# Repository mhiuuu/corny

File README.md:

# Corny Split Keyboard

My first custom split keyboard that takes inspiration from the [Corne keyboard](https://www.boardsource.xyz/products/Corne).

---

## Motivation

I’m pretty much a geek who always finds ways to create things tailored specifically for myself. I've been using Arch Linux (BTW), Hyprland (BTW), and Neovim (BTW) for over a year now, and most of my workflow depends heavily on the keyboard.

Over time, I’ve tried 60%, 75%, and 100% mechanical keyboards. They’re all nice, but I struggled to find space on my desk for schoolwork, and placing the keyboard on my laptop caused the battery to heat up. Then one day, I stumbled upon [this video](https://youtu.be/7UXsD7nSfDY?si=9aiY0pJiT80jEVwv), which sparked the idea—and here it is: my first-ever custom-built split keyboard. All the design work was done in less than 5 days.

---

## Build

This keyboard was created using [Ergogen](https://github.com/ergogen/ergogen), with extra helpful guidance from the [Flatfootfox tutorial](https://flatfootfox.com) and HunterCook—a genius and my friend on Discord.

The design is entirely customized for my hand movements and habits. It may not suit your typing style (or even mine, as this is my first attempt). All routing was done manually and can be found in the `ergogen/results/pcbs/` directory, not in `ergogen/output/pcbs`, which contains files auto-generated by Ergogen.

---

### 1. Layout

The layout was fully created inside [Ergogen](https://ergogen.ceoloide.com).

Here’s my initial design of _Corny_, drawn in Excalidraw:

It was draw in the first day with some adjustments. However, while working on the board I realized that I forgot the `{}` and the `FN` key so I have to make some changes

1. Adding one more thumb key to each side (It was 2 but I have enough place for all the key I need now)
2. Changing the `CAPSLOCK` to `FN` cuz who even use it now?

---

### 2. Components

For switches, I decided to use `MX switches` instead of `Choc switches` like most others, because MX switches are much easier to find in Vietnam. In fact, I couldn’t find any retailers selling Choc switches on the major e-commerce platforms here. My switch of choice is the [Akko Rosewood](https://en.akkogear.com/product/akko-rosewood-switch/).

> Choc switch (low profile): 17×18mm

> MX switch (The type of switch on normal mechanical keyboard): 19×19mm

For the MCU, I used the [nice!nano v2](https://typeractive.xyz/products/nice-nano?variant=42225114546407) for wireless functionality despite of the fact that you can see, yep obviously the MCU in the PCBS are `nice!nano_v1` but I could only find the version 2. However, you can use almost any available MCU, such as the [Pro Micro](https://hshop.vn/arduino-pro-micro) or even a [Raspberry Pi Zero](https://www.raspberrypi.com/products/raspberry-pi-zero/).

---

### 3. PCBs

The PCBs were auto-generated by [Ergogen](https://ergogen.ceoloide.com) in `.kicad_pcb` format, which you can open in [KiCad](https://www.kicad.org/). Be sure to connect all routes manually, and aim for an `unrouted` count of zero—otherwise, you'll have unconnected components (oops!).

I had a hard time with the PCBs when I was connecting everything and remembered that _damn this should not be here_ so make sure connecting all the important components first (hardest part) before working with the keys

The finished PCBs are located in `./PCBs/` not in `./ergogen/output/pcbs/`, they are auto generated by ergogen

Here are the final PCB designs:

| Left Plate                  | Right Plate                  |
| --------------------------- | ---------------------------- |
|  |  |

---

### 4. Cases

## Version 1:

Design the case inside ergogen is possible. However, it was a pain in the ass so I made a dirty (or genius?) move by making half of the case in ergogen, the eport it in `jscad` convert to `stl` using the `@jscad/cli@1` package and then put it inside [OnShape](https://cad.onshape.com) then delete the wrong part

Here is the image of the final `stl` file

| Left case                  | Right case                  |
| -------------------------- | --------------------------- |
|  |  |

P/s: Im praying that the mounting hole will fit

## Version 2:

The case was denied because it was just a basic outline which you can literally create anywhere using a case genereator. So I decided to sit back and start working with [OnShaped](https://cad.onshape.com) to design a new case.

First, I imported the `.dxf` files from the `./ergogen/output/outline` and lay it on to the sketch so that I can have a brief view of what the outlines are. (Disclaimer: the outline is 10 times the actual size so after all you have to scale it down) Then I extrude the parts I need to create a simple case as the `version_1`.

Then I have to create the nut for M2 screws but I had had a bad time with creating custom nut and screw so I decided to use the public version of a M2 nut and extrude it so that it has a little margin I need to stand the PCBs.

Next step is the worst step you can imagine, making the top plate!!! I had to redo the first step of making the case (creating a plate without the walls) the align it so that the keys hole and the plate aligned perfectly. Then I had to extrude each key individually!!!!! That is over 30 keys and yes it took a whooping amount of timeto do it. Also remember to cut the hole for the MCU to (you don't want to cut it manually when you got the 3D printed case tho)

Penultimate is the piercing hole for the velcro strap. This create 2 holes so that you can use the velcro strap to strap the keyboard around your leg when you are on a plane/train or just simply don't have the space for you keyboard.

Final parts are the detachable wrist rest using magnet. I use two 6mmx1.5mm magnet mounted to the case so that you can attach and remove the wrist rest with ease.

---

### 5. The software

I haven't had fund to get the parts yet but there is a tool called [zmk](/zmk-corny-config/) - I will keep the repo private for now since I am just doing it blindly without the physical parts

---

### 6. BOM

AYou can check the BOM in [here](/Corny_BOM.csv). As you can see, the prices look a bit messy—that's the best I could do when converting between VND and USD (inflation is killing me). Only Shopee Vietnam, a Vietnamese e-commerce platform, lists exact prices in VND, which I then converted to USD. All the other retailers charge in USD. Even more frustrating, Typeractive actually charges more in VND than in USD!

#### Electronics

| No. | Parts                    | Unit cost (USD) | Unit cost (VND) | Quantity | Retailer    | Shipping + Tax (USD) | Shipping + Tax (VND) | Total cost (USD) | Total cost (VND) | Source                                                                                                                                                                                                       | Note |
| --- | ------------------------ | --------------- | --------------- | -------- | ----------- | -------------------- | -------------------- | ---------------- | ---------------- | ------------------------------------------------------------------------------------------------------------------------------------------------------------------------------------------------------------ | ---- |
| 1   | Nice!nano MCU            | 25.41           | 662,000         | 2        | Typeractive | Free                 | Free                 | 50.82            | 1324000          | https://typeractive.xyz/products/nice-nano?variant=42225114546407                                                                                                                                            |      |
| 2   | Power Switch             | 1.54            | 40,000          | 1        | Typeractive | Free                 | Free                 | 1.54             | 40000            | https://typeractive.xyz/products/power-switch?variant=45597854171367                                                                                                                                         |      |
| 3   | Diodes                   | 0.77            | 20,000          | 6        | Typeractive | Free                 | Free                 | 5.62             | 120000           | https://typeractive.xyz/products/smd-diodes?variant=45597514858727                                                                                                                                           |      |
| 4   | Reset button             | 1.54            | 40,000          | 1        | Typeractive | Free                 | Free                 | 1.54             | 40000            | https://typeractive.xyz/products/reset-button?variant=45597784932583                                                                                                                                         |      |
| 5   | Battery jack             | 1.04            | 27,000          | 1        | Typeractive | Free                 | Free                 | 1.04             | 27000            | https://typeractive.xyz/products/battery-jack?_pos=2&_psq=bat&_ss=e&_v=1.0                                                                                                                                   |      |
| 6   | Machine Sockets and Pins | 6.61            | 172,000         | 2        | Typeractive | Free                 | Free                 | 13.22            | 344000           | https://typeractive.xyz/products/machine-sockets-and-pins?variant=45741664469223                                                                                                                             |      |
| 7   | Kailh Hotswap Sockets    | 1.54            | 40,000          | 6        | Typeractive | Free                 | Free                 | 9.24             | 240000           | https://typeractive.xyz/products/hotswap-sockets?_pos=1&_psq=hot&_ss=e&_v=1.0                                                                                                                                |      |
| 8   | PCBs                     | 10.7            | 278,960         | 2        | JLCPCB      | 12.47                | 324,470              | 33.87            | 882390           | https://jlcpcb.com                                                                                                                                                                                           |      |
| 9   | Battery                  | 1.53            | 39,820          | 2        | Shopee VN   | 0.39                 | 10,000               | 3.45             | 89640            | https://shopee.vn/Ehbqna-103450-Pin-s%E1%BA%A1c-lithium-polymer-lipo-3.7V-2000MAH-m%E1%BB%9Bi-i.240549284.26978776277?sp_atk=05b7ba61-e00c-4b50-957d-6faa2f0e17b5&xptdk=05b7ba61-e00c-4b50-957d-6faa2f0e17b5 |      |

**Electronics Total**: **119.34 USD** / **3,107,030 VND**

#### Hardware

| No. | Parts             | Unit cost (USD) | Unit cost (VND) | Quantity | Retailer  | Shipping + Tax (USD) | Shipping + Tax (VND) | Total cost (USD) | Total cost (VND) | Source                                                                                                                                                                                                                                                                                                                                                                                                                 | Note  |
| --- | ----------------- | --------------- | --------------- | -------- | --------- | -------------------- | -------------------- | ---------------- | ---------------- | ---------------------------------------------------------------------------------------------------------------------------------------------------------------------------------------------------------------------------------------------------------------------------------------------------------------------------------------------------------------------------------------------------------------------- | ----- |
| 1   | Akko Rosewood     | 0.29            | 7,499           | 60       | Shopee VN | 0.64                 | 16,500               | 18.04            | 466440           | https://shopee.vn/Switch-Akko-Cream-V3-Pro-Yellow-Blue-Piano-Silent-Fairy-Linear-Penguin-Tactile-Switch-Akko-Cream-Yellow-Blue-DoDo-Gear-i.665488736.23277505182?xptdk=5d8c6d42-8fd7-4eb1-abab-defb630a23ef                                                                                                                                                                                                            |       |
| 2   | Keycaps           | 0.38            | 9,900           | 58       | Shopee VN | 0.71                 | 18,300               | 22.75            | 592500           | https://shopee.vn/-Cherry-Keycap-Blank-1u-Trong-Su%E1%BB%91t-N%C3%BAt-Keycap-L%E1%BA%BB-Trong-Su%E1%BB%91t-Cho-B%C3%A0n-Ph%C3%ADm-C%C6%A1-Switch-Tester-YMDK-Cherry-Profile-i.250643057.21084233969?sp_atk=5da32bc9-29da-4c23-a1d6-5834020310b1&xptdk=5da32bc9-29da-4c23-a1d6-5834020310b1                                                                                                                             |       |
| 3   | Solder            | 2.49            | 65,000          | 1        | Shopee VN | 0.64                 | 16,500               | 3.13             | 81500            | https://shopee.vn/Thi%E1%BA%BFc-H%C3%A0n-63-37-SN63-Flux-1.8-Cu%E1%BB%99n-50G-i.27117857.29208587865                                                                                                                                                                                                                                                                                                                   |       |
| 4   | Soldering station | N/A             | N/A             | N/A      | Owned     | -                    | -                    | -                | -                |                                                                                                                                                                                                                                                                                                                                                                                                                        | Owned |
| 5   | 3D printed cases  | 13.78           | 358,556         | 1        | JLCPCB    | Free                 | Free                 | 13.78            | 358,556          | https://jlcpcb.com                                                                                                                                                                                                                                                                                                                                                                                                     |       |
| 6   | Tenting feet      | 2.45            | 63,800          | 2        | Shopee VN | 0.58                 | 15,000               | 4.9              | 142600           | https://shopee.vn/Mini-Di-%C4%90%E1%BB%99ng-H%E1%BB%A3p-Kim-K%E1%BA%BDm-Laptop-%C4%90%E1%BB%A9ng-B%C3%A0n-Ph%C3%ADm-M%C3%A1y-T%C3%ADnh-Ch%C3%A2n-Gi%C3%A1-%C4%90%E1%BB%A1-Cho-Macbook-Air-Huawei-Xiaomi-Notebook-C%C3%B3-Th%E1%BB%83-G%E1%BA%ADp-L%E1%BA%A1i-%C4%90%E1%BB%83-B%C3%A0n-%C4%90%E1%BB%A9ng-i.196261835.26757041641?sp_atk=357ebaeb-0b03-477a-85da-ad89e47e8870&xptdk=357ebaeb-0b03-477a-85da-ad89e47e8870 |       |

**Hardware Total**: **62.6 USD** / **1,641,596 VND**

---

### 💰 TOTAL COST

-   **Electronics**: 3,107,030 VND / 119.34 USD
-   **Hardware**: 1,641,596 VND / 62.6 USD
-   **Grand Total**: **4,748,626 VND / 181.94 USD**

_Disclaimer: When you try to converting VND to USD you can see that they are about ~1 dollar away from each other. It is because you can not accurately convert the price down to every cent._

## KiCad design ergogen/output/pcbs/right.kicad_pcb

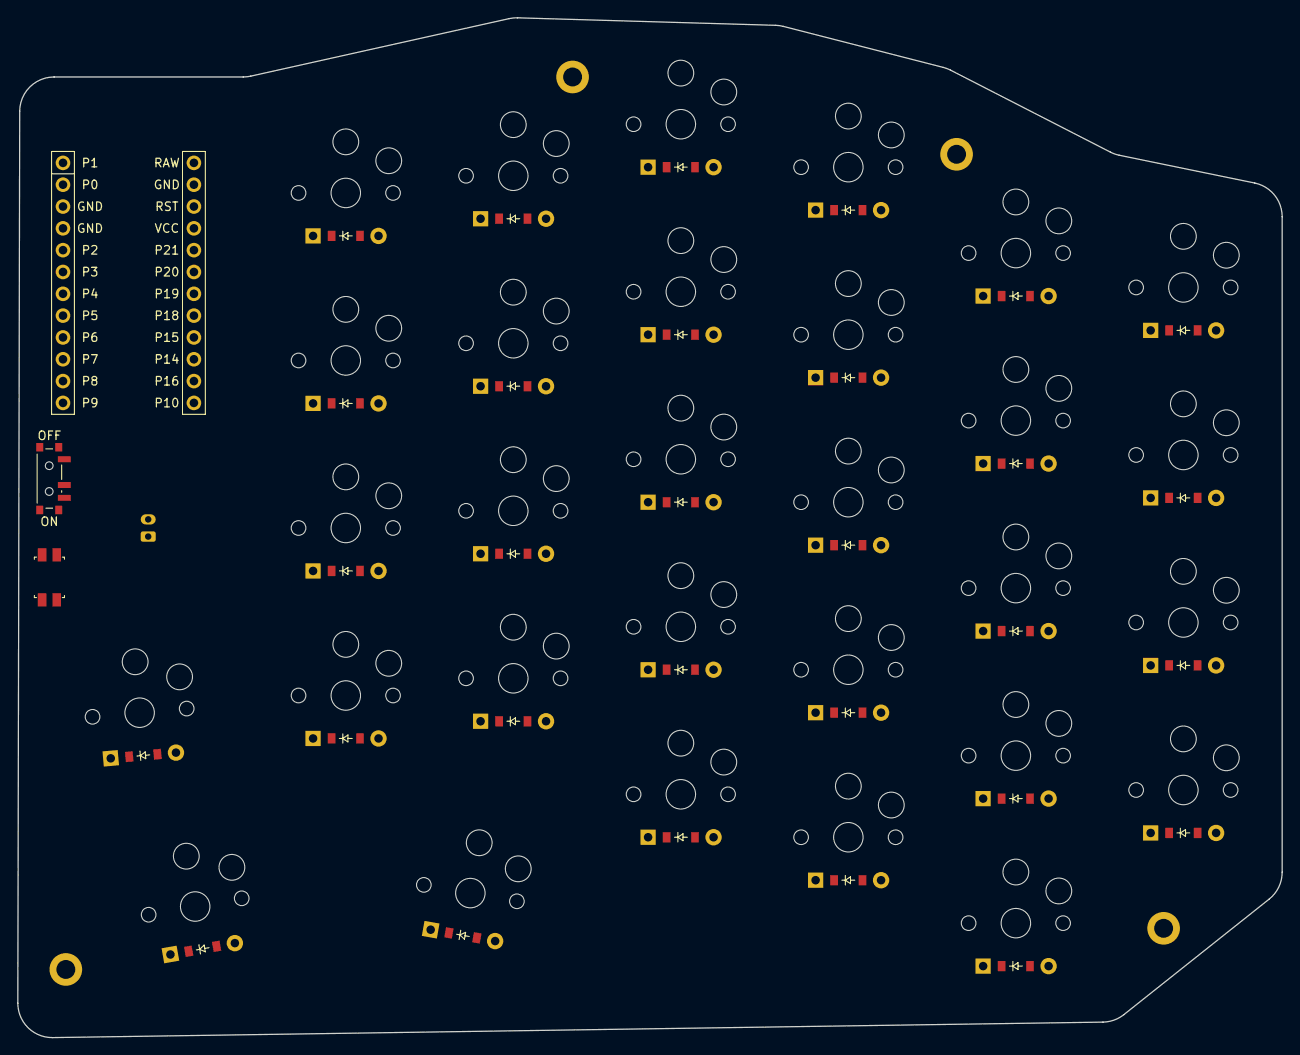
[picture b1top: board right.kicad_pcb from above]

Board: 2 copper layers, 147.2 x 118.7 mm, 68 parts (1 on the bottom side), 46 nets, no tracks yet.

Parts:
D1, D2, D3, D4, D5, D6, D7, D8, D9, D10, D11, D12, D13, D14, D15, D16, D17, D18, D19, D20, D21, D22, D23, D24, D25, D26, D27, D28, D29, D30: ComboDiode
H1, H2, H3, H4: mounting_hole_plated
JST1: battery_connector_jst_ph_2
MCU1: mcu_nice_nano
PWR1: power_switch_smd_side
RST1: reset_switch_smd_side
S1, S2, S3, S4, S5, S6, S7, S8, S9, S10, S11, S12, S13, S14, S15, S16, S17, S18, S19, S20, S21, S22, S23, S24, S25, S26, S27, S28, S29, S30: PG1350

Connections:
BAT_P: JST1.2, PWR1.3
GND: JST1.1, MCU1.2, MCU1.21, MCU1.22, RST1.1, RST1.3
P3: D4.1, D9.1, D14.1, D19.1, D23.1, D27.1, MCU1.19
P4: D3.1, D8.1, D13.1, D18.1, D22.1, D26.1, MCU1.18
P5: D2.1, D7.1, D12.1, D17.1, D21.1, D25.1, MCU1.17
P6: D5.1, D10.1, D15.1, D28.1, D29.1, MCU1.16
P7: D1.1, D6.1, D11.1, D16.1, D20.1, D24.1, D30.1, MCU1.15
P10: MCU1.12, S29.1, S30.1
P14: MCU1.10, S20.1, S21.1, S22.1, S23.1, S28.1
P15: MCU1.9, S15.1, S16.1, S17.1, S18.1, S19.1
P16: MCU1.11, S24.1, S25.1, S26.1, S27.1
P18: MCU1.8, S10.1, S11.1, S12.1, S13.1, S14.1
P19: MCU1.7, S5.1, S6.1, S7.1, S8.1, S9.1
P20: MCU1.6, S1.1, S2.1, S3.1, S4.1
RAW: MCU1.1, PWR1.2
RST: MCU1.3, RST1.2, RST1.4
mirror_index_row0: D20.2, S20.2
mirror_index_row1: D21.2, S21.2
mirror_index_row2: D22.2, S22.2
mirror_index_row3: D23.2, S23.2
mirror_inner_row0: D24.2, S24.2
mirror_inner_row1: D25.2, S25.2
mirror_inner_row2: D26.2, S26.2
mirror_inner_row3: D27.2, S27.2
mirror_long_thumbs: D29.2, S29.2
mirror_middle_arrow: D15.2, S15.2
mirror_middle_row0: D16.2, S16.2
mirror_middle_row1: D17.2, S17.2
mirror_middle_row2: D18.2, S18.2
mirror_middle_row3: D19.2, S19.2
mirror_near_thumbs: D28.2, S28.2
mirror_one_bracket: D30.2, S30.2
mirror_outer_row0: D1.2, S1.2
mirror_outer_row1: D2.2, S2.2
mirror_outer_row2: D3.2, S3.2
mirror_outer_row3: D4.2, S4.2
mirror_pinky_arrow: D5.2, S5.2
mirror_pinky_row0: D6.2, S6.2
mirror_pinky_row1: D7.2, S7.2
mirror_pinky_row2: D8.2, S8.2
mirror_pinky_row3: D9.2, S9.2
mirror_ring_arrow: D10.2, S10.2
mirror_ring_row0: D11.2, S11.2
mirror_ring_row1: D12.2, S12.2
mirror_ring_row2: D13.2, S13.2
mirror_ring_row3: D14.2, S14.2

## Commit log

2025-06-05 docs(README): Add BOM in table format, some journals
2025-06-05 assets(left/right_plate): rename the plate to the correct side
2025-06-05 docs(README): Add case section
2025-06-05 docs(README): pcbs instruction / feat(pcbs): add finished pcbs files
2025-06-06 file(3D): move to the root folder / feat(add): Add image to the PCBs
2025-06-09 file(3D): add new 3D case version / file(BOM): update BOM / doc(README): update case designing journal, BOM
2025-06-11 file(Journal): Add journal
2025-06-11 fix(JOURNAL): fix grammar
